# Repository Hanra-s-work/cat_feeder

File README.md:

<!-- 
-- +==== BEGIN CatFeeder =================+
-- LOGO: 
-- ..............(..../\\
-- ...............)..(.')
-- ..............(../..)
-- ...............\\(__)|
-- Inspired by Joan Stark
-- source https://www.asciiart.eu/
-- animals/cats
-- /STOP
-- PROJECT: CatFeeder
-- FILE: README.md
-- CREATION DATE: 16-10-2025
-- LAST Modified: 14:25:19 04-12-2025
-- DESCRIPTION: 
-- This is the project in charge of making the connected cat feeder project work.
-- /STOP
-- COPYRIGHT: (c) Cat Feeder
-- PURPOSE: The readme file of the project
-- // AR
-- +==== END CatFeeder =================+
-->
# Cat Feeder — Docker Compose helper

 This repository contains the backend for the Cat Feeder project and helper files to run it via Docker Compose.

 This README explains how to start the compose stack, what components are required, which environment files the project uses, and provides simple examples for Linux and Windows.

## Required components

- Docker (Engine) — install from <https://docs.docker.com/get-docker/>
- Docker Compose v2 (integrated as `docker compose`) or `docker-compose` (v1) fallback

 Optional but recommended:

- Add your user to the `docker` group to avoid using sudo for Docker commands (Linux).

## Files of interest

- [`start_compose.sh`](start_compose.sh) — POSIX shell script to start/stop the compose stack (Linux/macOS). Now contains Doxygen-style comments.
- [`start_compose.bat`](start_compose.bat) — Windows batch equivalent. Also contains Doxygen-style comments.
- [`docker/dockerfile.backend`](docker/dockerfile.backend) — Dockerfile used to build the backend image; now annotated with Doxygen-style header comments.
- [`.env`](.env) and [`sample.env`](sample.env) — environment variables used by the server and the image build. Note: if the compose manifest references `.env` (or any other env files), Docker Compose expects them to exist and will fail if a referenced file is missing.
- [`docker/.db.env`](docker/.db.env), [`docker/.redis.env`](docker/.redis.env) — service-specific env files referenced by the compose config. If the compose manifest references these files and they are missing, `docker compose` may fail to start the stack.

### Generating documentation (Doxygen)

The repository includes Doxygen *generation* scripts and assets in [doxygen_generation/](doxygen_generation/) (this folder contains the Dockerfile, Doxyfile and helper scripts used to produce the documentation). The generated HTML output will be written to [documentation/](documentation/) by the generator. Handwritten/manual docs are maintained in [manual_documentation/](manual_documentation/).

See [`manual_documentation/QUICK_START.md`](./manual_documentation/QUICK_START.md) for the full quickstart. Key steps summarized here:

```bash
# Make the generator scripts executable (one-time)
chmod +x doxygen_generation/generate_docs.sh doxygen_generation/make_documentation.sh

# Recommended: pull the prebuilt Doxygen image first (fast, ~3-4 minutes):
docker pull hanralatalliard/doxygen:latest || true

# Generate the docs (run from repository root). The script will attempt to pull the
# prebuilt image and will only build locally if necessary:
./doxygen_generation/generate_docs.sh

# Serve the generated HTML locally (preferred using Docker httpd):
docker run --rm --name Cat Feeder_docs -p 8080:80 \
 -v "$(pwd)/documentation/html":/usr/local/apache2/htdocs/:ro \
 httpd:2.4
# Open http://localhost:8080

# Notes:
# - If Docker requires root on your machine, prefix commands with `sudo`.
# - Building the Docker image locally may trigger a full LaTeX build; compiling
#   LaTeX/PDF artifacts from source can take several hours (~4h). Prefer pulling
#   the prebuilt image and build locally only as a last resort.
```

## Environment variables

### Important variables used at runtime include

- DB_HOST, DB_PORT, DB_USER, DB_PASSWORD, DB_DATABASE — database connection
- REDIS_PASSWORD, REDIS_SOCKET — redis connection
- PORT, HOST — server bind settings (default: PORT=5000, HOST=0.0.0.0)
- DEBUG — whether to launch the server in debug mode
- LOG_SERVER_DATA, LOG_PATH, LOG_DATA — logging configuration

 When running with Docker Compose, the compose file will pick up `.env` from the repository root and any additional env files referenced by the compose manifest (for example `docker/.db.env` or `docker/.redis.env`). If a referenced env file is missing, Docker Compose may fail. The included `start_compose.sh` script will create reasonable default env files (`.env`, `docker/.db.env`, `docker/.redis.env`) when first run to help avoid this problem.

## How to start the Docker Compose stack

 Choose the platform you're on.

 Linux / macOS (recommended):

 1. Make sure Docker is installed and your user can access the Docker daemon. If not, run the script with sudo or add your user to the `docker` group.
 2. From the repository root run:

 ```bash
 chmod +x ./start_compose.sh && ./start_compose.sh
 ```

 This script will:

- check Docker and Compose availability
- create `.env`, `docker/.db.env`, `docker/.redis.env` if missing
- create `docker/db/data` and `docker/redis/data` directories if missing
- run `docker compose -f ./docker-compose.yaml down` then
- run `docker compose -f ./docker-compose.yaml up --build`

 If your system does not allow running docker without sudo, the script will try to use `sudo` transparently and prompt for a password if needed.

 Windows (PowerShell / CMD):

 Run from repository root in a Command Prompt:

 ```batch
 start_compose.bat
 ```

 The batch file mirrors the Linux script’s behavior, checks for Docker availability and launches the compose stack. On Windows, administrative privileges may be required depending on your Docker Desktop configuration.

## Notes about the Dockerfile and scripts

- `docker/dockerfile.backend` contains the image build logic. It builds a Python virtual environment inside the image, installs dependencies from `requirements.txt`, and creates a small launcher script to run the server.
- `start_compose.sh`, `start_compose.bat`, and the Dockerfile now include Doxygen-style headers to make it easier to generate documentation or scan file metadata.

## Troubleshooting

- Permission denied while accessing Docker? Add your Linux user to the `docker` group:

 ```bash
 sudo usermod -aG docker $USER
 # then re-login or run: newgrp docker
 ```

- Docker Compose command not found? Install Docker Compose v2 (usually included in modern Docker Desktop/Engine) or install `docker-compose` separately.

- If you changed `PORT` in `.env` and the container binding needs updating, verify `docker-compose.yaml` port mappings match your desired host port.

## Contributions

Please visit [`CONTRIBUTING.md`](./CONTRIBUTING.md) and [`COMMIT_CONVENTION.md`](./COMMIT_CONVENTION.md) to check the rules and norms of the repository.

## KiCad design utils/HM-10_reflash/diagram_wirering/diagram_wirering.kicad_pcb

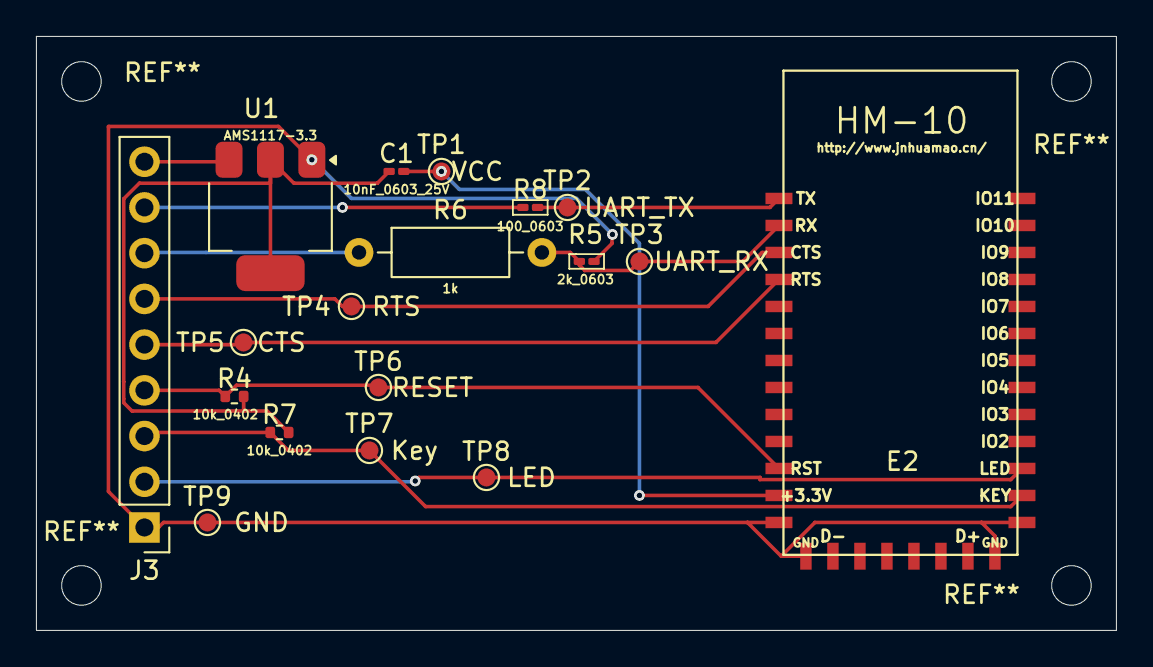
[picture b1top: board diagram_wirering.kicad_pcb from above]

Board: 2 copper layers, 60.0 x 33.0 mm, 18 parts (0 on the bottom side), 13 nets.

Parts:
C1: 10nF_0603_25V; C_0201_0603Metric_Pad0.64x0.40mm_HandSolder
E2: HM-10; 26.9X13X2.2_BOARD
J3: PINHD_1x9_Male; PinHeader_1x09_P2.54mm_Vertical
R4, R7: 10k_0402; R_0402_1005Metric
R5: 2k_0603; R_0201_0603Metric_Pad0.64x0.40mm_HandSolder
R6: 1k; R_Axial_DIN0207_L6.3mm_D2.5mm_P10.16mm_Horizontal
R8: 100_0603; R_0201_0603Metric_Pad0.64x0.40mm_HandSolder
TP1: VCC; TestPoint_Pad_D1.0mm
TP2: UART_TX; TestPoint_Pad_D1.0mm
TP3: UART_RX; TestPoint_Pad_D1.0mm
TP4: RTS; TestPoint_Pad_D1.0mm
TP5: CTS; TestPoint_Pad_D1.0mm
TP6: RESET; TestPoint_Pad_D1.0mm
TP7: Key; TestPoint_Pad_D1.0mm
TP8: LED; TestPoint_Pad_D1.0mm
TP9: GND; TestPoint_Pad_D1.0mm
U1: AMS1117-3.3; SOT-223-3_TabPin2

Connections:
/breakout_board_uart/CTS (D5): E2.4 (UART_RTS), J3.5, TP5.1
/breakout_board_uart/GND (ARDUINO): E2.13 (GND), E2.14 (GND), E2.21 (GND), E2.22 (GND), J3.1, R5.2, TP9.1, U1.1 (GND)
/breakout_board_uart/KEY (D7): E2.23 (KEY), J3.3, R7.1, TP7.1
/breakout_board_uart/LED (D8): E2.24 (LED), J3.2, TP8.1
/breakout_board_uart/RESET (D6): E2.11 (RESET), J3.4, R4.1, TP6.1
/breakout_board_uart/RTS (D4): E2.3 (UART_CTS), J3.6, TP4.1
/breakout_board_uart/RX (D2): J3.8, R8.1
/breakout_board_uart/TX (D3): J3.7, R6.1
/breakout_board_uart/UART_RX (HM-10): E2.2 (UART_RX), R5.1, R6.2, TP3.1
/breakout_board_uart/UART_TX (HM-10): E2.1 (UART_TX), R8.2, TP2.1
/breakout_board_uart/VCC 3.3-7v: J3.9, U1.3 (VI)
/breakout_board_uart/VCC (3.3V) (HM-10): C1.2, E2.12 (+3.3V), TP1.1
unnamed: C1.1, R4.2, R7.2, U1.2 (VO)

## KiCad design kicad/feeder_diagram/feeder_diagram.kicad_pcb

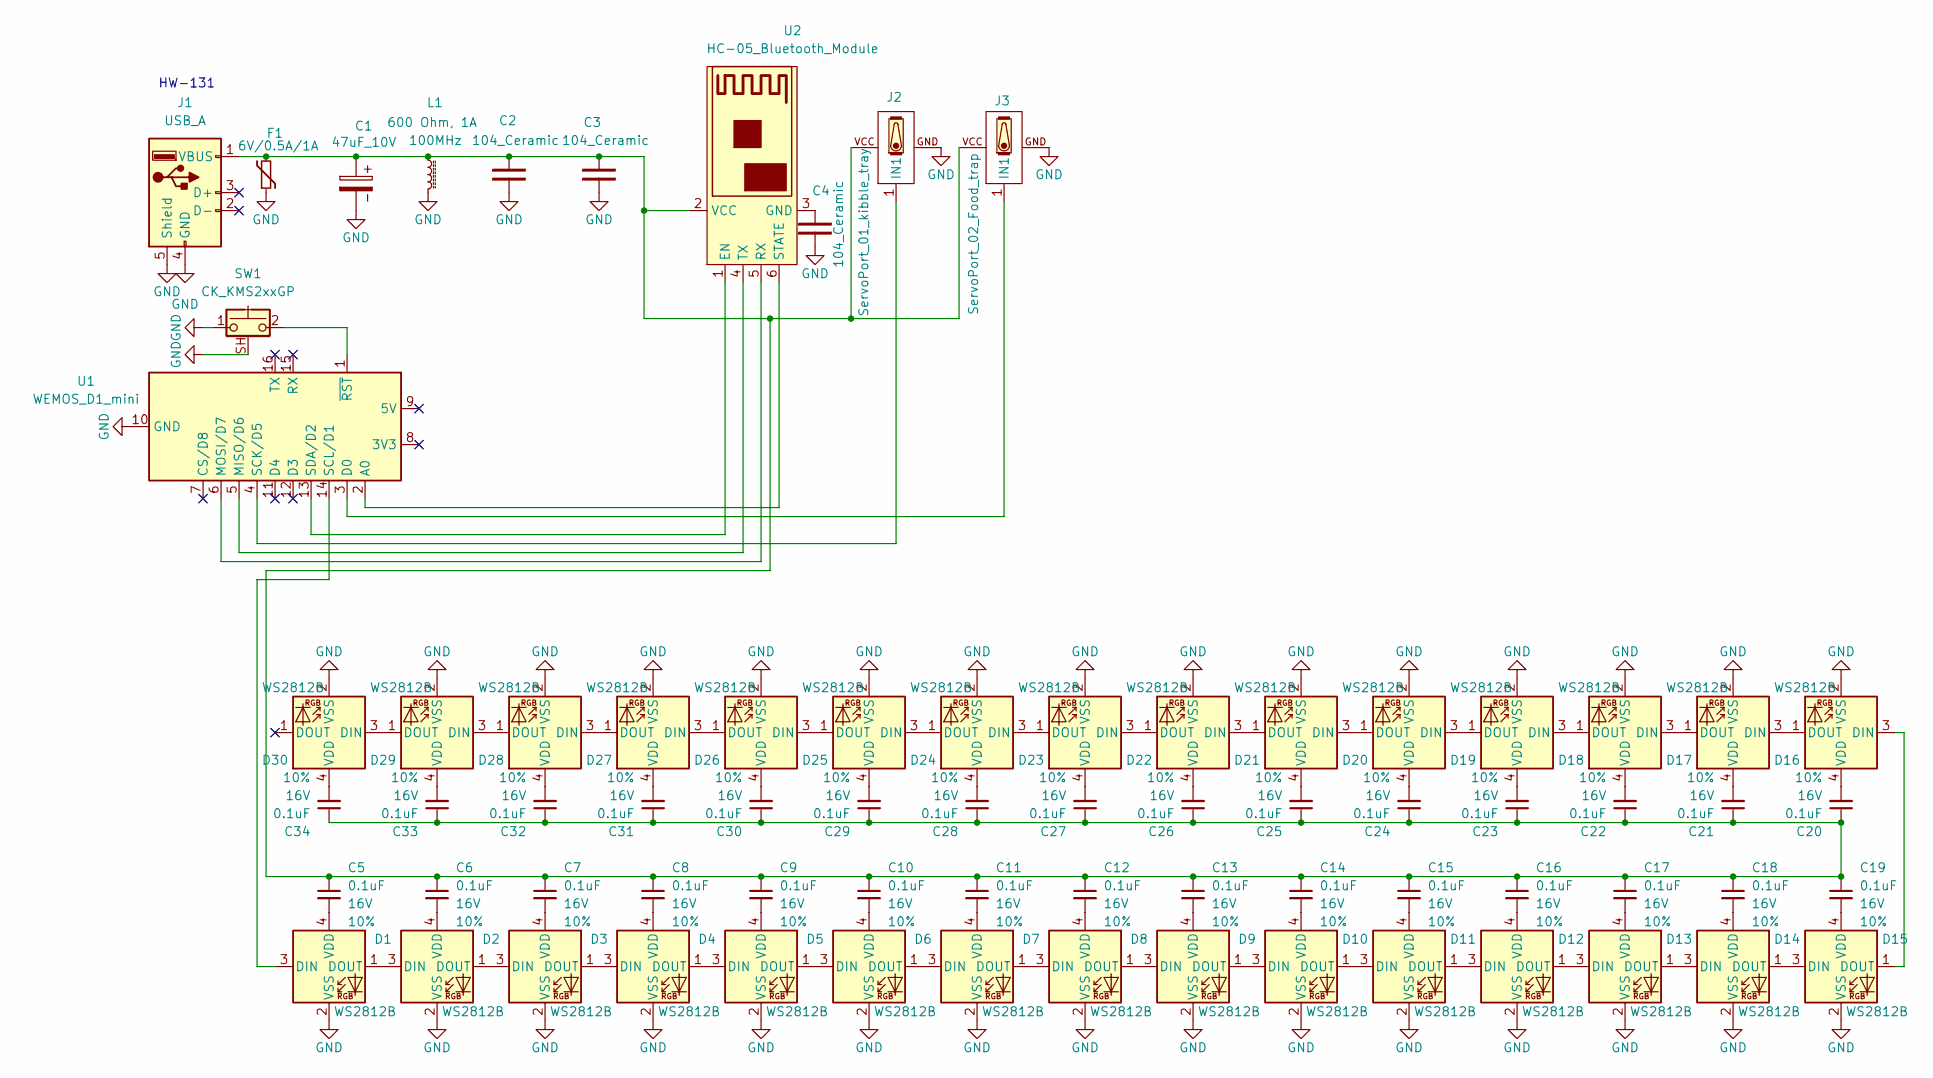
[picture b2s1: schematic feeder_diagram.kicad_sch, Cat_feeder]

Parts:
C1: 47uF_10V; CP_Radial_D4.0mm_P1.50mm
C2, C3, C4: 104_Ceramic; C_Disc_D5.0mm_W2.5mm_P2.50mm
C5, C6, C7, C8, C9, C10, C11, C12, C13, C14, C15, C16, C17, C18, C19, C20, C21, C22, C23, C24, C25, C26, C27, C28, C29, C30, C31, C32, C33, C34: 0.1uF; C_0402_1005Metric; Voltage 16V; Tolerance 10%
D1, D2, D3, D4, D5, D6, D7, D8, D9, D10, D11, D12, D13, D14, D15, D16, D17, D18, D19, D20, D21, D22, D23, D24, D25, D26, D27, D28, D29, D30: WS2812B; WS2812_2020
F1: 6V/0.5A/1A; 0805
J1: USB_A; USB_A_Connfly_DS1095
J2: ServoPort_01_kibble_tray; ServoPort_01_Vertical
J3: ServoPort_02_Food_trap; ServoPort_01_Vertical
L1: 600 Ohm, 1A; L_6.3x6.3_H3
SW1: CK_KMS2xxGP; SW_SPST_CK_KMS2xxGP
U1: WEMOS_D1_mini; WEMOS_D1_mini_light
U2: HC-05_Bluetooth_Module

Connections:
GND: C1.2, C2.1, C3.1, C4.1, D1.2 (VSS), D2.2 (VSS), D3.2 (VSS), D4.2 (VSS), D5.2 (VSS), D6.2 (VSS), D7.2 (VSS), D8.2 (VSS), D9.2 (VSS), D10.2 (VSS), D11.2 (VSS), D12.2 (VSS), D13.2 (VSS), D14.2 (VSS), D15.2 (VSS), D16.2 (VSS), D17.2 (VSS), D18.2 (VSS), D19.2 (VSS), D20.2 (VSS), D21.2 (VSS), D22.2 (VSS), D23.2 (VSS), D24.2 (VSS), D25.2 (VSS), D26.2 (VSS), D27.2 (VSS), D28.2 (VSS), D29.2 (VSS), D30.2 (VSS), F1.1, J1.4 (GND), J1.5 (Shield), J2.GND, J3.GND, L1.2, SW1.1, SW1.SH (B), U1.10 (GND)
unnamed: D1.3 (DIN), U1.14 (SCL/D1)
unnamed: D1.1 (DOUT), D2.3 (DIN)
unnamed: C5.2, D1.4 (VDD)
unnamed: D2.1 (DOUT), D3.3 (DIN)
unnamed: C6.2, D2.4 (VDD)
unnamed: D3.1 (DOUT), D4.3 (DIN)
unnamed: C7.2, D3.4 (VDD)
unnamed: D4.1 (DOUT), D5.3 (DIN)
unnamed: C8.2, D4.4 (VDD)
unnamed: D5.1 (DOUT), D6.3 (DIN)
unnamed: C9.2, D5.4 (VDD)
unnamed: D6.1 (DOUT), D7.3 (DIN)
unnamed: C10.2, D6.4 (VDD)
unnamed: D7.1 (DOUT), D8.3 (DIN)
unnamed: C11.2, D7.4 (VDD)
unnamed: D8.1 (DOUT), D9.3 (DIN)
unnamed: C12.2, D8.4 (VDD)
unnamed: C13.2, D9.4 (VDD)
unnamed: D9.1 (DOUT), D10.3 (DIN)
unnamed: D10.1 (DOUT), D11.3 (DIN)
unnamed: C14.2, D10.4 (VDD)
unnamed: D11.1 (DOUT), D12.3 (DIN)
unnamed: C15.2, D11.4 (VDD)
unnamed: D12.1 (DOUT), D13.3 (DIN)
unnamed: C16.2, D12.4 (VDD)
unnamed: D13.1 (DOUT), D14.3 (DIN)
unnamed: C17.2, D13.4 (VDD)
unnamed: D14.1 (DOUT), D15.3 (DIN)
unnamed: C18.2, D14.4 (VDD)
unnamed: D15.1 (DOUT), D16.3 (DIN)
unnamed: C19.2, D15.4 (VDD)
unnamed: D16.1 (DOUT), D17.3 (DIN)
unnamed: C20.2, D16.4 (VDD)
unnamed: D17.1 (DOUT), D18.3 (DIN)
unnamed: C21.2, D17.4 (VDD)
unnamed: D18.1 (DOUT), D19.3 (DIN)
unnamed: C22.2, D18.4 (VDD)
unnamed: D19.1 (DOUT), D20.3 (DIN)
unnamed: C23.2, D19.4 (VDD)
unnamed: D20.1 (DOUT), D21.3 (DIN)
unnamed: C24.2, D20.4 (VDD)
unnamed: D21.1 (DOUT), D22.3 (DIN)
unnamed: C25.2, D21.4 (VDD)
unnamed: D22.1 (DOUT), D23.3 (DIN)
unnamed: C26.2, D22.4 (VDD)
unnamed: D23.1 (DOUT), D24.3 (DIN)
unnamed: C27.2, D23.4 (VDD)
unnamed: D24.1 (DOUT), D25.3 (DIN)
unnamed: C28.2, D24.4 (VDD)
unnamed: D25.1 (DOUT), D26.3 (DIN)
unnamed: C29.2, D25.4 (VDD)
unnamed: D26.1 (DOUT), D27.3 (DIN)
unnamed: C30.2, D26.4 (VDD)
unnamed: D27.1 (DOUT), D28.3 (DIN)
unnamed: C31.2, D27.4 (VDD)
unnamed: D28.1 (DOUT), D29.3 (DIN)
unnamed: C32.2, D28.4 (VDD)
unnamed: D29.1 (DOUT), D30.3 (DIN)
unnamed: C33.2, D29.4 (VDD)
unnamed: C34.2, D30.4 (VDD)
unnamed: C1.1, C2.2, C3.2, C5.1, C6.1, C7.1, C8.1, C9.1, C10.1, C11.1, C12.1, C13.1, C14.1, C15.1, C16.1, C17.1, C18.1, C19.1, C20.1, C21.1, C22.1, C23.1, C24.1, C25.1, C26.1, C27.1, C28.1, C29.1, C30.1, C31.1, C32.1, C33.1, C34.1, F1.2, J1.1 (VBUS), J2.VCC, J3.VCC, L1.1, U2.2 (VCC)
unnamed: J2.1 (IN1), U1.4 (SCK/D5)
unnamed: J3.1 (IN1), U1.3 (D0)
unnamed: U1.2 (A0), U2.6 (STATE)
unnamed: U1.5 (MISO/D6), U2.4 (TX)
unnamed: U1.6 (MOSI/D7), U2.5 (RX)
unnamed: U1.13 (SDA/D2), U2.1 (EN)
unnamed: SW1.2, U1.1 (~RST)
unnamed: C4.2, U2.3 (GND)

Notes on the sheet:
HW-131

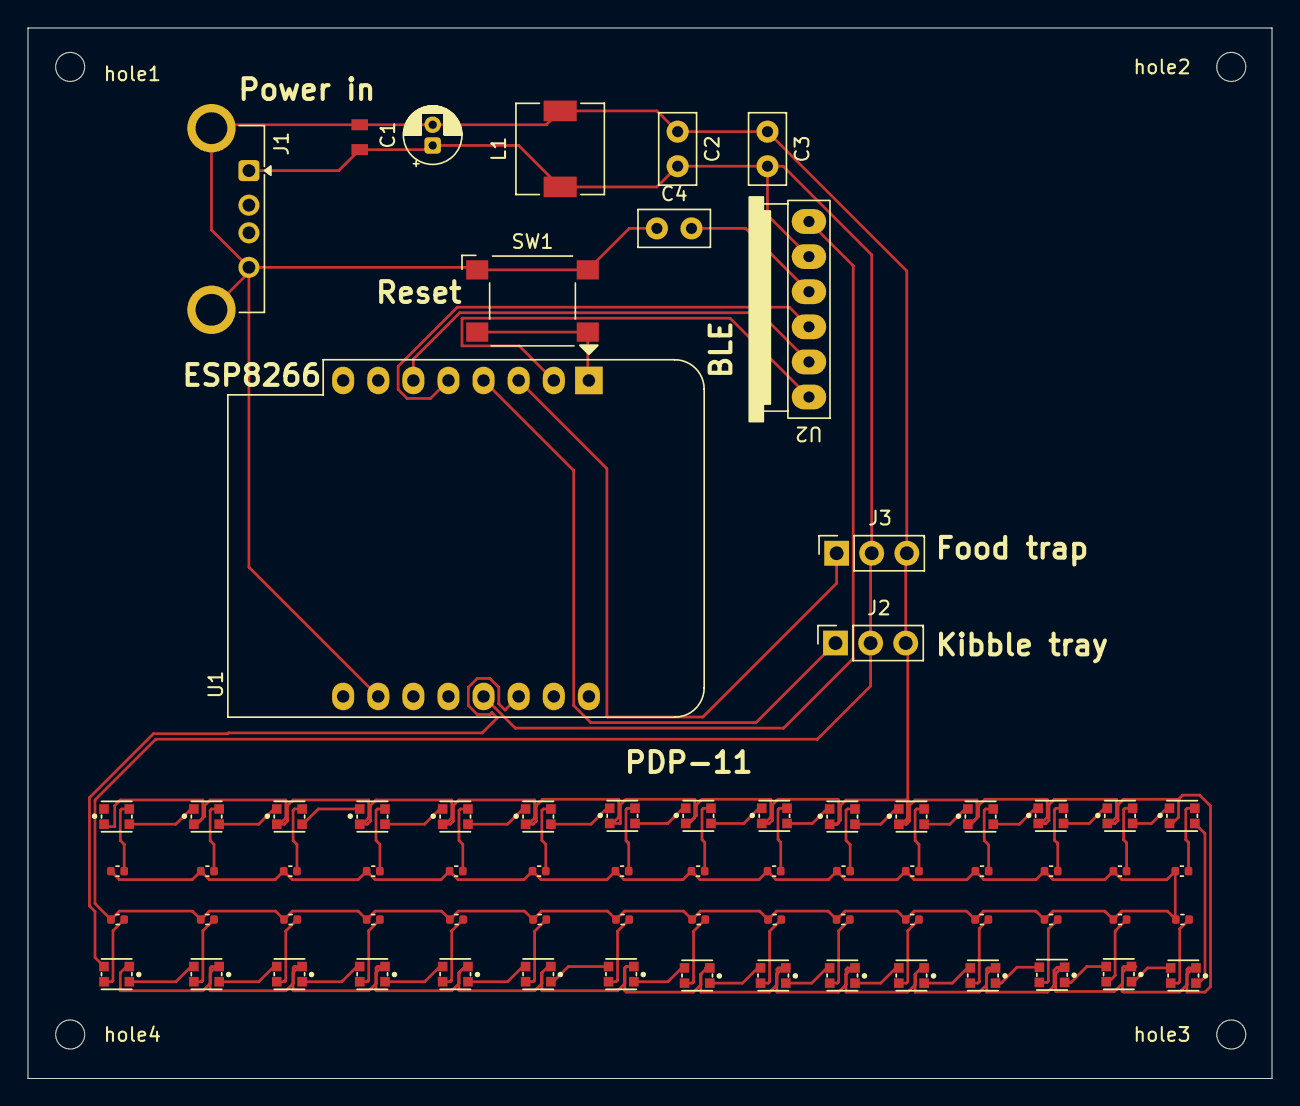
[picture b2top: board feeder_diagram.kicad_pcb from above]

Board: 2 copper layers, 90.0 x 76.0 mm, 76 parts (0 on the bottom side), 70 nets.

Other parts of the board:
hole1, hole2, hole3, hole4: MountingHole_2.1mm

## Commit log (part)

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2025-12-03 chore: initial Commit
2025-12-03 chore: add .github
2025-12-04 [UPDATE] the file signatures and structure
2025-12-08 [ADD] a bash script to help dump sql databases to files for reference and restoration later on
2025-12-08 [UPDATE] the icon of the server
2025-12-11 [UPDATE] the test suit to be able to test the server classes
2025-12-11 [ADD] a set of tests to make sure the http status codes are correct
2025-12-11 [UPDATE] the injection class to let valid e-mails pass throughwhike stopping potential phony @ shenaniganry
2025-12-11 [UPDATE] the unit test code for the test_http_codes not to import modules in the functions and only in the main section of the document
2025-12-11 [UPDATE] the database table content and configuration
2025-12-11 [UPDATE] the doxygen workflow (to hopfully free enough space for the container to be pulled)
2025-12-13 [UPDATE] the sql injection to be more resilient with e-mails
2025-12-13 [FIX] the false positive on e-mail checking in the sql injection checking
2025-12-13 [UPDATE] the docstrings in the test_sql_injection suite
2025-12-13 [FIX] the e-mail detection issue and some false positives found along the way
2025-12-14 [UPDATE] tests for the sql injection library and the sanitisation functions
2025-12-14 [FIX] an issue with the sanitisation function
2025-12-14 [FIX] issue where the sql tests would fail if not launched from the proper directory
2025-12-14 [UPDATE] the unit tests regarding the injection prevention so that the uuid passed as token would not be considered as vulnerable
2025-12-14 [FIX] http_code testing file wrapper issues
2025-12-14 [ADD] working login and register endpoints
2025-12-15 [FIX] linting issue
2026-01-22 [ADD] big server and security update
2026-01-22 [UPDATE] the cat feeder's database
2026-01-22 [UPDATE] the database dump structure
2026-01-22 [UPDATE] endpoints for the beacons and feeders
2026-01-22 [ADD] current implementation progress of the beacon and feeder endpoints
2026-01-23 [ADD] the endpoints to handle the pet definition
2026-01-23 [ADD] the post feeder visit endpoint
2026-01-23 [ADD] updates to the path manager to allow it to support meta-data decorators for endpoint documentation
2026-01-23 [ADD] wrappers to provide additional endpoint data to the dynamic documentation api's
2026-01-23 [REFACTOR] security decorators and [UPDATE] OpenAPI schema generation
    - [UPDATE] security decorators to accept parameters for security level and environment.
    - [ADD] a new OpenAPIBuilder class for extracting metadata and building OpenAPI documentation.
    - [UPDATE] the endpoint metadata extraction in PathManager to be simpler by utilizing the OpenAPIBuilder class.
    - [UPDATE] error handling and logging during route injection in PathManager.
    - [REMOVE] redundant metadata extraction methods and streamlined the process for better maintainability.
2026-01-24 [FIX] structure display issue
2026-01-24 [ADD] seperate endpoint functions for '', '/' and '/api/v1'
2026-01-24 [ADD] a is_path_registered and add_path_if_not_exists functions to path_manager
2026-01-24 [FIX] path issues with the constants file regarding the favicon
2026-01-24 [ADD] the put_feeder_ip endpoint
2026-01-24 [UPDATE] the doc processor to hopefully not duplicate endpoints during registration
2026-01-24 [UPDATE] function names to contain uuid's to prevent duplicate issues
2026-01-24 [UPDATE] function operation id's in the endpoint manager
2026-01-24 [UPDATE] the beacon endpoints to have one function per method
2026-01-24 [UPDATE] the logic to handle the openapi interface development
2026-01-24 [REMOVE] unused import
2026-01-24 [UPDATE] the headers to match the versions provided by the header extension
2026-01-24 [ADD] a tiny front-end handler to allow primitive interraction with the backend
2026-01-24 [ADD] pico.css for styling in the backend's asset folder
2026-01-25 [ADD] an emoji font to support custom emojis in every browser
2026-01-25 [ADD] the login page for the simple front-end
2026-01-25 [ADD] a placeholder page for the dashboard page
2026-01-25 [ADD] a simple logout page
2026-01-25 [FIX] http codes error that was preventing them from injecting raw file content when a query is made
2026-01-25 [ADD] a config line in the config file to allow control over the caching duration of the asset files
2026-01-25 [ADD] the front-end asset endpoints required by the front-end pages
2026-01-25 [UPDATE] the endpoints to have sample bodies when they require them
2026-01-25 [FIX] verification issue (where function was expecting endpoint to be run by an administrator
2026-01-25 [ADD] the new endpoints for the new functions
2026-01-25 [ADD] emoji support
2026-01-25 [ADD] a few missing description bodies
2026-01-25 [FIX] user information gathering in the cat_endpoint
2026-01-25 [FIX] the hid/show password button issue
2026-01-25 [ADD] the html code for the dashboard page
2026-01-25 [FIX] a certain amount of querying issues in the dashboard javascript code
2026-01-26 [UPDATE] the content response to be more flexible when the mime type is a file, otherwise, behaviour unchanged
2026-01-30 [ADD] the kicad diagram so the circuit wirering can be followed
2026-01-31 [ADD] the current state of the code for the esp8266
2026-01-31 [UPDATE] the sql database
2026-01-31 [UPDATE] the get_pets endpoint to call appropriate columns in the database
2026-01-31 [FIX] SQL error calls in the cat_endpoint file
2026-01-31 [FIX] different endpoint issues
2026-01-31 [ADD] a cron job to reset the food counters every 24 hours
2026-01-31 [FIX] the /api/v1/feeders endpoint
2026-01-31 [REMOVE] unused parameter from the endpoint documentation
2026-01-31 [ADD] a debug line to display the raw list before cleaning in the clean_list function
2026-01-31 [FIX] borken SQL status checking
2026-02-01 [ADD] logging and temporarily disabled the backend health check
2026-02-01 [UPDATE] the sql_query_boilerplate to check complex WHERE clauses
2026-02-01 [UPDATE] the SQL where parser to be more robust
2026-02-01 [FIX] token check issues in non_web
2026-02-02 [ADD] tests and robustness to the where parametisation checking
2026-02-02 [UPDATE] the location of the imports to be bellow the file heading
2026-02-02 [ADD] missing docstring
2026-02-05 [ADD] more sanitisation functions for http responses
2026-02-05 [UPDATE] the feeder to automatically clean content before returning it
2026-02-05 [FIX] the endpoint to allow the refresh of the data in the endpoint
2026-02-05 [FIX] the pet registration endpoint
2026-02-05 [UPDATE] the website to display the content into tables
2026-02-05 [FIX] data gathering issues about the pet endpoints
2026-02-05 [UPDATE] the recent activity section
2026-02-05 [FIX] parsing issue in the beautifier function when '*' is passed or a column name
2026-02-05 [UPDATE] the get_pet endpoint to be less redundant in it's calls
2026-02-06 [FIX] beautify table function
2026-02-06 [UPDATE] the .gitignore to keep all required files for the esp8266 build to work
2026-02-06 [ADD] an environement handler middleware
2026-02-07 [ADD] a script to dynamically inject the environement variables during compilation time (in a shadow way so that they are not pushed on the repository)
2026-02-07 [UPDATE] the logo to use a unicode / so that there were no warnings during compilation
2026-02-07 [ADD] missing header's to the files.
2026-02-11 [ADD] a custom << operator overload to avoid using the Arduino String as much as possible while retaining as much functionality as possible.
2026-02-11 [REFACTOR] the code to use the least possible amount of calls to the String command
2026-02-11 [UPDATE] the ble class handler to hopefully communicate correctly with the ble board
2026-02-12 [FIX] memory and ble issues
2026-02-12 [ADD] a postman collection to help with knowing the server endpoints
2026-02-12 [FIX] potential communication issues
2026-02-12 [UPDATE] the bluetooth module to be hopefully more memory efficient
2026-02-13 [ADD] latest version of the ble debug attempts
2026-02-14 [REMOVE] cache file that seems to have slipped in
2026-02-14 [ADD] a new field to the environement
2026-02-14 [ADD] the endpoints that the esp needs to communicate with the server
2026-02-14 [ADD] the required call for sending a sign of life to the control server
2026-02-14 [ADD] food dispensing logic
2026-02-14 [UPDATE] the setup logic to not check motor calibration as it would offset them
2026-02-16 [UPDATE] the food dispensing logic to be asynchronous
2026-02-16 [ADD] code to try and get the ble to work
2026-02-16 [REMOVE] kicad cache
2026-02-17 [ADD] an override endpoint for the demo
2026-02-18 [ADD] the latest version of the program
